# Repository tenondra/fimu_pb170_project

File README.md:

W:/pb170_project/doc/user_manual.md

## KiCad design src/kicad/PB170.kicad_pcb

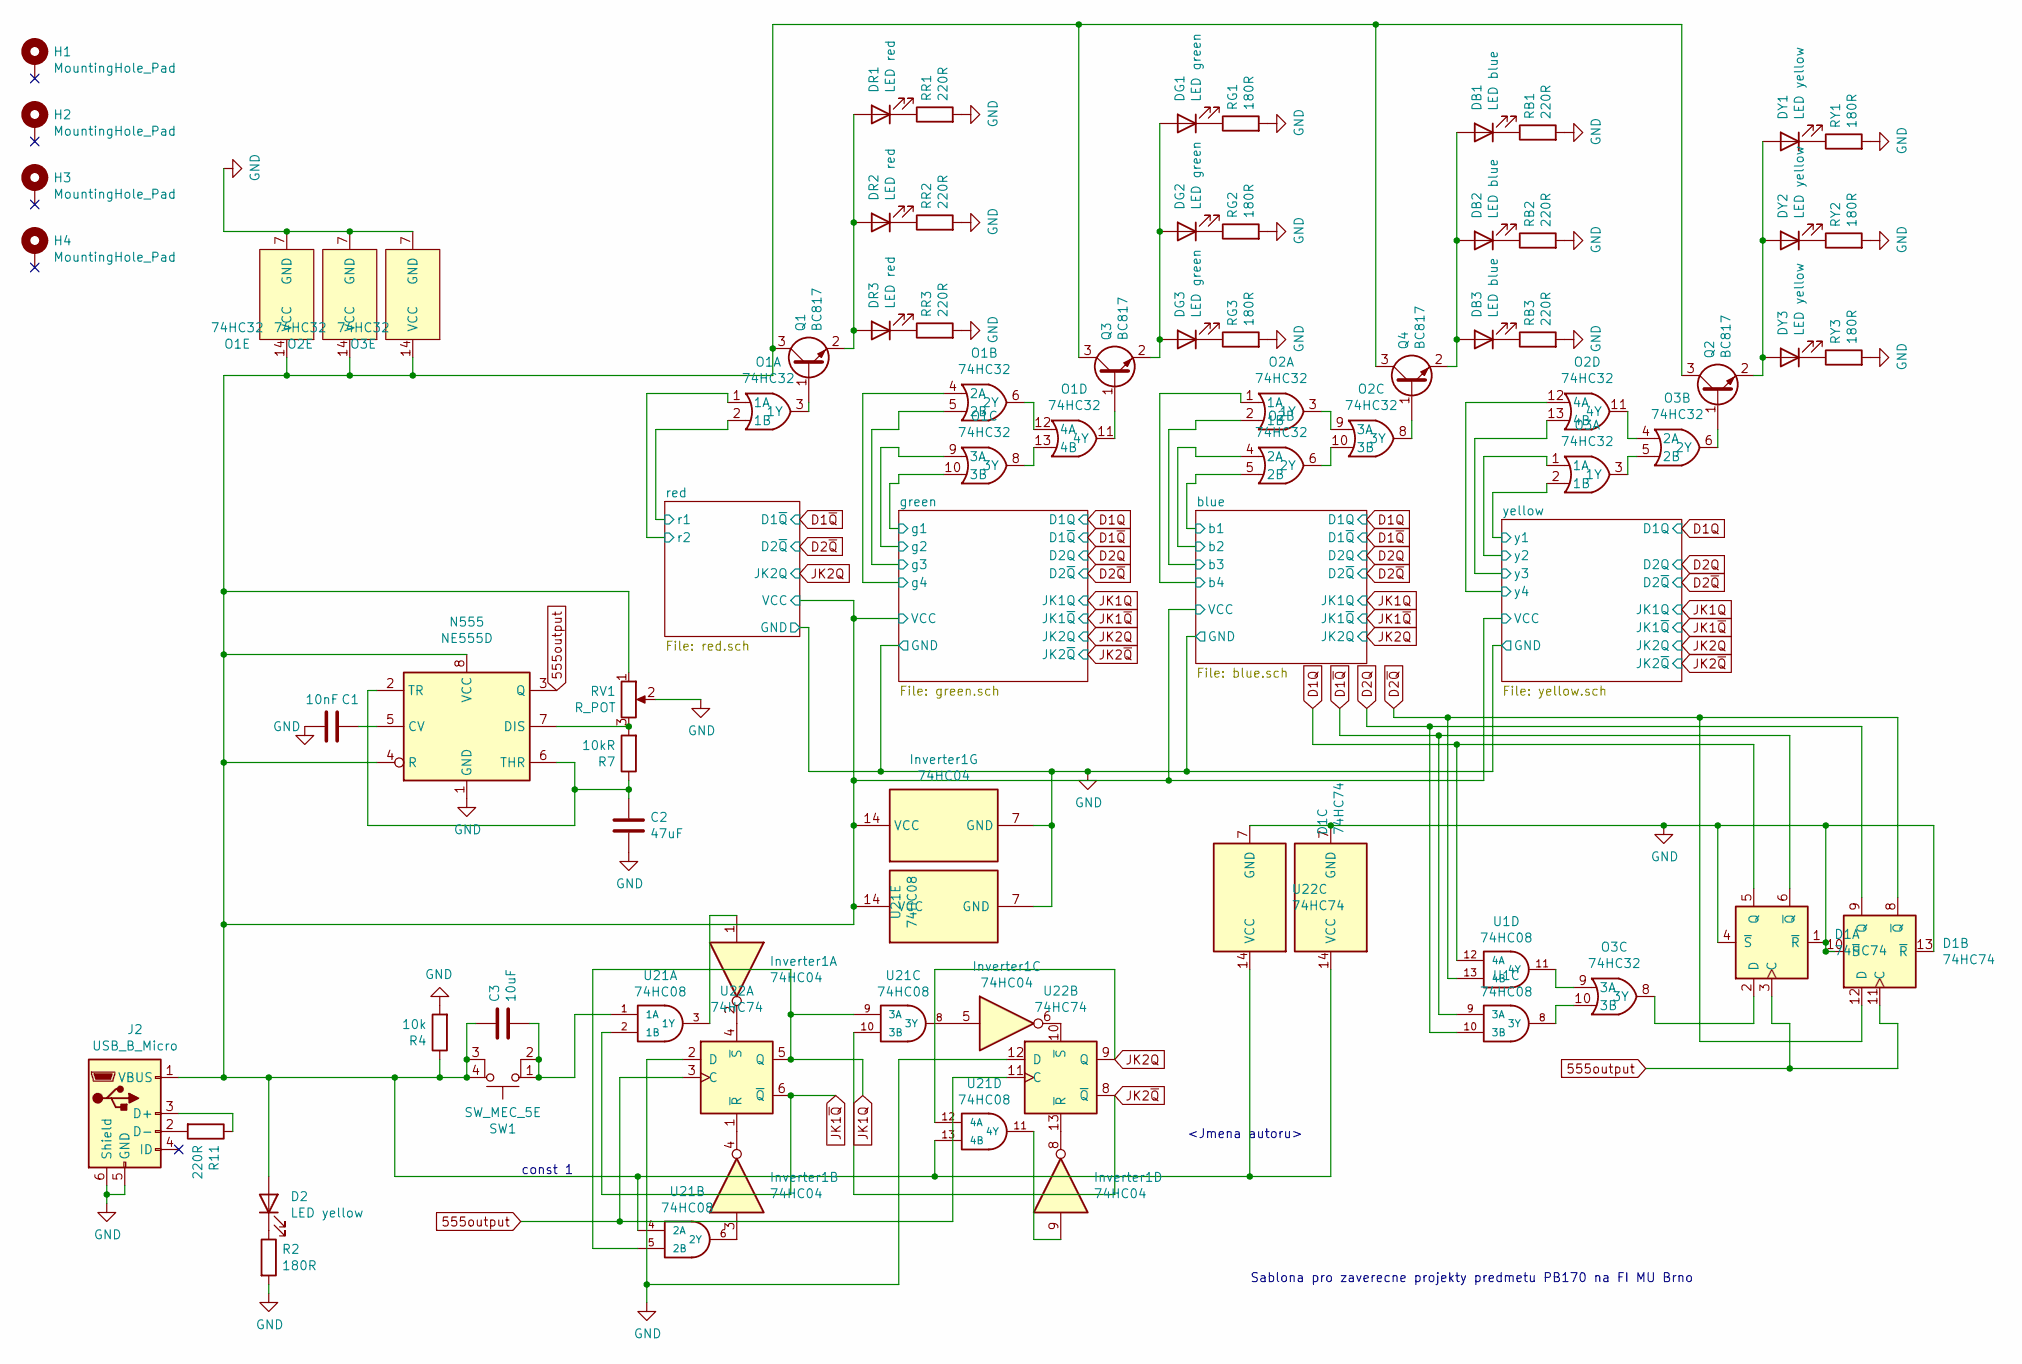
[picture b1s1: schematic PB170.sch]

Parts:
C1: 10nF; C_0805_2012Metric; LCSC C1710
C2: 47uF; C_1206_3216Metric; LCSC C96123
C3: 10uF; C_0805_2012Metric; LCSC C15850
D1: 74HC74; HTSSOP-14-1EP_4.4x5mm_P0.65mm_EP3.4x5mm_Mask3x3.1mm
D2: LED yellow; LED_0603_1608Metric; LCSC C72038
DB1, DB2, DB3: LED blue; LED_0603_1608Metric; LCSC C72041
DG1, DG2, DG3: LED green; LED_0603_1608Metric; LCSC C72043
DR1, DR2, DR3: LED red; LED_0603_1608Metric; LCSC C2286
DY1, DY2, DY3: LED yellow; LED_0603_1608Metric; LCSC C72038
H1, H2, H3, H4: MountingHole_Pad; MountingHole_3.2mm_M3_Pad
Inverter1: 74HC04; SOIC-14_3.9x8.7mm_P1.27mm
J2: USB_B_Micro; MICRO-USB-SMD_MICROXNJ; LCSC C404969
N555: NE555D; SOIC-8_3.9x4.9mm_P1.27mm; LCSC C7593
O1, O2, O3: 74HC32; SOIC-14_3.9x8.7mm_P1.27mm; LCSC C5632
Q1, Q2, Q3, Q4: BC817; SOT-23
R2: 180R; R_0603_1608Metric; LCSC C22828
R4: 10k; R_0603_1608Metric; LCSC C25804
R7: 10kR; R_0603_1608Metric; LCSC C25804
R11: 220R; R_0603_1608Metric; LCSC C22962
RB1, RB2, RB3: 220R; R_0603_1608Metric; LCSC C22962
RG1, RG2, RG3: 180R; R_0603_1608Metric; LCSC C22828
RR1, RR2, RR3: 220R; R_0603_1608Metric; LCSC C22962
RV1: R_POT; potentiometer10k; LCSC C132879
RY1, RY2, RY3: 180R; R_0603_1608Metric; LCSC C22828
SW1: SW_MEC_5E; TactileSwitch_C381064; LCSC C381064
U1, U21: 74HC08; SOIC-14_3.9x8.7mm_P1.27mm; LCSC C5593
U22: 74HC74; HTSSOP-14-1EP_4.4x5mm_P0.65mm_EP3.4x5mm_Mask3x3.1mm; LCSC C6761

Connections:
555output: D1.3 (C), D1.11 (C), N555.3 (Q), U22.3 (C), U22.11 (C)
/blue/VCC: C3.1, D1.14 (VCC), D2.2 (A), Inverter1.14 (VCC), J2.1 (VBUS), N555.4 (R), N555.8 (VCC), O1.14 (VCC), O2.14 (VCC), O3.14 (VCC), Q1.3 (C), Q2.3 (C), Q3.3 (C), Q4.3 (C), R4.1, RV1.1, SW1.3 (K), SW1.4 (A), U21.4 (2A), U21.13 (4B), U21.14 (VCC), U22.14 (VCC); also elsewhere on the board
/blue/b1: O2.5 (2B); also elsewhere on the board
/blue/b2: O2.4 (2A); also elsewhere on the board
/blue/b3: O2.2 (1B); also elsewhere on the board
/blue/b4: O2.1 (1A); also elsewhere on the board
/green/g1: O1.10 (3B); also elsewhere on the board
/green/g2: O1.9 (3A); also elsewhere on the board
/green/g3: O1.5 (2B); also elsewhere on the board
/green/g4: O1.4 (2A); also elsewhere on the board
/red/r1: O1.2 (1B); also elsewhere on the board
/red/r2: O1.1 (1A); also elsewhere on the board
/yellow/y1: O3.2 (1B); also elsewhere on the board
/yellow/y2: O3.1 (1A); also elsewhere on the board
/yellow/y3: O2.13 (4B); also elsewhere on the board
/yellow/y4: O2.12 (4A); also elsewhere on the board
D1Q: D1.5 (Q), U1.12 (4A); also elsewhere on the board
D1~Q: D1.6 (~Q), U1.9 (3A); also elsewhere on the board
D2Q: D1.9 (Q), U1.10 (3B); also elsewhere on the board
D2~Q: D1.8 (~Q), D1.12 (D), U1.13 (4B); also elsewhere on the board
GND: C1.2, C2.2, D1.1 (~R), D1.4 (~S), D1.7 (GND), D1.10 (~S), D1.13 (~R), Inverter1.7 (GND), J2.5 (GND), J2.6 (Shield), N555.1 (GND), O1.7 (GND), O2.7 (GND), O3.7 (GND), R2.2, R4.2, RB1.2, RB2.2, RB3.2, RG1.2, RG2.2, RG3.2, RR1.2, RR2.2, RR3.2, RV1.2, RY1.2, RY2.2, RY3.2, U21.7 (GND), U22.2 (D), U22.7 (GND), U22.12 (D); also elsewhere on the board
JK1Q: U21.5 (2B), U21.9 (3A), U22.5 (Q); also elsewhere on the board
JK1~Q: U21.2 (1B), U22.6 (~Q); also elsewhere on the board
JK2Q: U21.12 (4A), U22.9 (Q); also elsewhere on the board
JK2~Q: U21.10 (3B), U22.8 (~Q); also elsewhere on the board
unnamed: C1.1, N555.5 (CV)
unnamed: C2.1, N555.2 (TR), N555.6 (THR), R7.1
unnamed: C3.2, SW1.1, SW1.2, U21.1 (1A)
unnamed: D1.2 (D), O3.8 (3Y)
unnamed: D2.1 (K), R2.1
unnamed: DB1.1 (K), RB1.1
unnamed: DB1.2 (A), DB2.2 (A), DB3.2 (A), Q4.2 (E)
unnamed: DB2.1 (K), RB2.1
unnamed: DB3.1 (K), RB3.1
unnamed: DG1.1 (K), RG1.1
unnamed: DG1.2 (A), DG2.2 (A), DG3.2 (A), Q3.2 (E)
unnamed: DG2.1 (K), RG2.1
unnamed: DG3.1 (K), RG3.1
unnamed: DR1.1 (K), RR1.1
unnamed: DR1.2 (A), DR2.2 (A), DR3.2 (A), Q1.2 (E)
unnamed: DR2.1 (K), RR2.1
unnamed: DR3.1 (K), RR3.1
unnamed: DY1.1 (K), RY1.1
unnamed: DY1.2 (A), DY2.2 (A), DY3.2 (A), Q2.2 (E)
unnamed: DY2.1 (K), RY2.1
unnamed: DY3.1 (K), RY3.1
unnamed: Inverter1.1, U21.3 (1Y)
unnamed: Inverter1.2, U22.4 (~S)
unnamed: Inverter1.3, U21.6 (2Y)
unnamed: Inverter1.4, U22.1 (~R)
unnamed: Inverter1.5, U21.8 (3Y)
unnamed: Inverter1.6, U22.10 (~S)
unnamed: Inverter1.8, U22.13 (~R)
unnamed: Inverter1.9, U21.11 (4Y)
unnamed: J2.2 (D-), R11.2
unnamed: J2.3 (D+), R11.1
unnamed: N555.7 (DIS), R7.2, RV1.3
unnamed: O1.3 (1Y), Q1.1 (B)
unnamed: O1.11 (4Y), Q3.1 (B)
unnamed: O1.6 (2Y), O1.12 (4A)
unnamed: O1.8 (3Y), O1.13 (4B)
unnamed: O2.3 (1Y), O2.9 (3A)
unnamed: O2.8 (3Y), Q4.1 (B)
unnamed: O2.6 (2Y), O2.10 (3B)
unnamed: O2.11 (4Y), O3.4 (2A)
unnamed: O3.3 (1Y), O3.5 (2B)
unnamed: O3.6 (2Y), Q2.1 (B)
unnamed: O3.9 (3A), U1.11 (4Y)
unnamed: O3.10 (3B), U1.8 (3Y)

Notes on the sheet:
Sablona pro zaverecne projekty predmetu PB170 na FI MU Brno
<Jmena autoru>
const 1

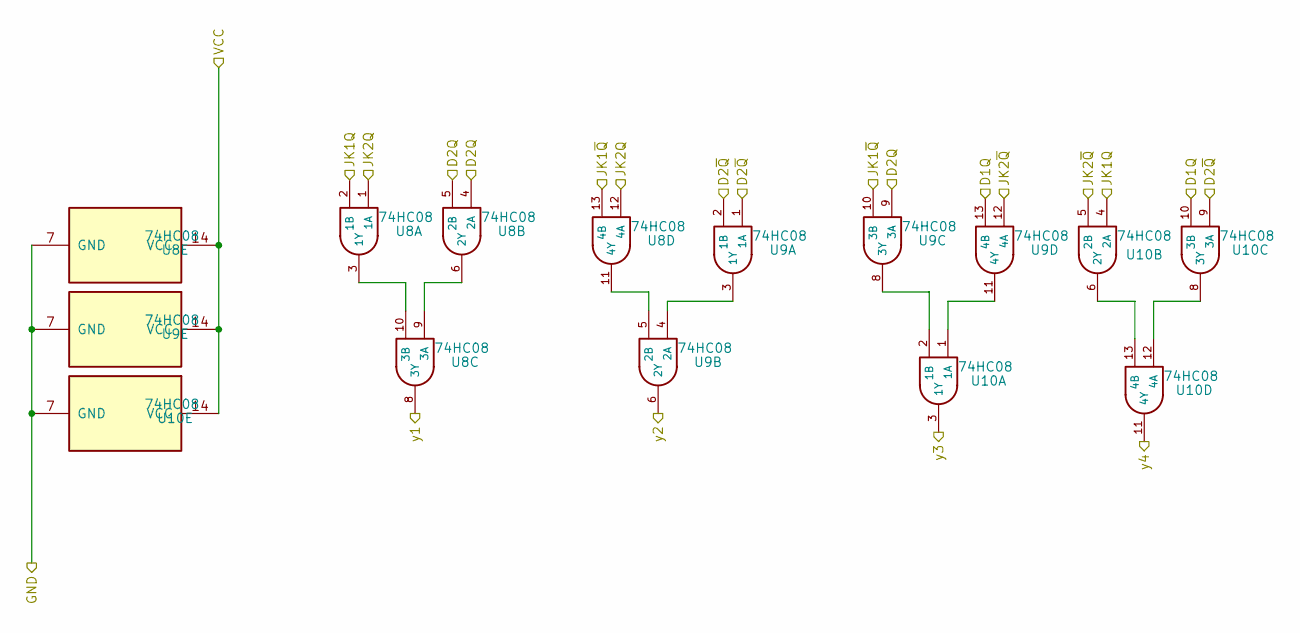
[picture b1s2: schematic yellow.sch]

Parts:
U8, U9, U10: 74HC08; SOIC-14_3.9x8.7mm_P1.27mm; LCSC C5593

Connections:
/blue/VCC: U8.14 (VCC), U9.14 (VCC), U10.14 (VCC); also elsewhere on the board
/yellow/y1: U8.8 (3Y); also elsewhere on the board
/yellow/y2: U9.6 (2Y); also elsewhere on the board
/yellow/y3: U10.3 (1Y); also elsewhere on the board
/yellow/y4: U10.11 (4Y); also elsewhere on the board
D1Q: U9.13 (4B), U10.10 (3B); also elsewhere on the board
D2Q: U8.4 (2A), U8.5 (2B), U9.9 (3A); also elsewhere on the board
D2~Q: U9.1 (1A), U9.2 (1B), U10.9 (3A); also elsewhere on the board
GND: U8.7 (GND), U9.7 (GND), U10.7 (GND); also elsewhere on the board
JK1Q: U8.2 (1B), U10.4 (2A); also elsewhere on the board
JK1~Q: U8.13 (4B), U9.10 (3B); also elsewhere on the board
JK2Q: U8.1 (1A), U8.12 (4A); also elsewhere on the board
JK2~Q: U9.12 (4A), U10.5 (2B); also elsewhere on the board
unnamed: U8.6 (2Y), U8.9 (3A)
unnamed: U8.3 (1Y), U8.10 (3B)
unnamed: U8.11 (4Y), U9.5 (2B)
unnamed: U9.3 (1Y), U9.4 (2A)
unnamed: U9.11 (4Y), U10.1 (1A)
unnamed: U9.8 (3Y), U10.2 (1B)
unnamed: U10.8 (3Y), U10.12 (4A)
unnamed: U10.6 (2Y), U10.13 (4B)

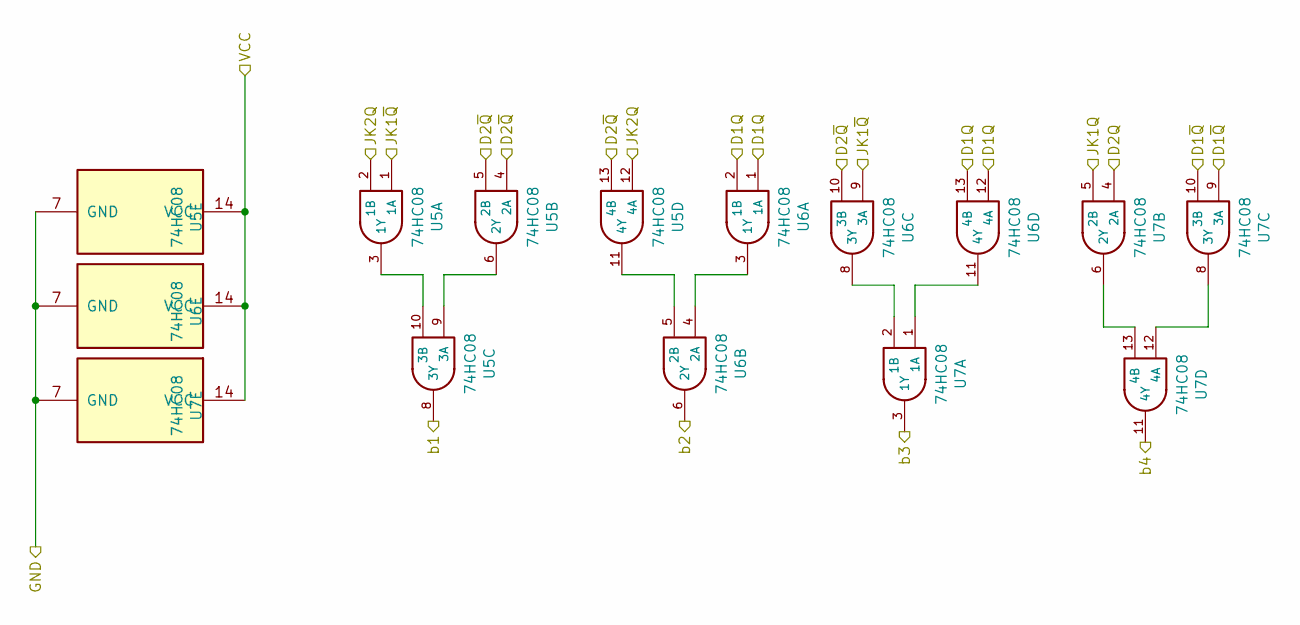
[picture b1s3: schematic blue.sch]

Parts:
U5, U6, U7: 74HC08; SOIC-14_3.9x8.7mm_P1.27mm; LCSC C5593

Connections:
/blue/VCC: U5.14 (VCC), U6.14 (VCC), U7.14 (VCC); also elsewhere on the board
/blue/b1: U5.8 (3Y); also elsewhere on the board
/blue/b2: U6.6 (2Y); also elsewhere on the board
/blue/b3: U7.3 (1Y); also elsewhere on the board
/blue/b4: U7.11 (4Y); also elsewhere on the board
D1Q: U6.1 (1A), U6.2 (1B), U6.12 (4A), U6.13 (4B); also elsewhere on the board
D1~Q: U7.9 (3A), U7.10 (3B); also elsewhere on the board
D2Q: U7.4 (2A); also elsewhere on the board
D2~Q: U5.4 (2A), U5.5 (2B), U5.13 (4B), U6.10 (3B); also elsewhere on the board
GND: U5.7 (GND), U6.7 (GND), U7.7 (GND); also elsewhere on the board
JK1Q: U7.5 (2B); also elsewhere on the board
JK1~Q: U5.1 (1A), U6.9 (3A); also elsewhere on the board
JK2Q: U5.2 (1B), U5.12 (4A); also elsewhere on the board
unnamed: U5.6 (2Y), U5.9 (3A)
unnamed: U5.3 (1Y), U5.10 (3B)
unnamed: U5.11 (4Y), U6.5 (2B)
unnamed: U6.3 (1Y), U6.4 (2A)
unnamed: U6.8 (3Y), U7.2 (1B)
unnamed: U6.11 (4Y), U7.1 (1A)
unnamed: U7.8 (3Y), U7.12 (4A)
unnamed: U7.6 (2Y), U7.13 (4B)

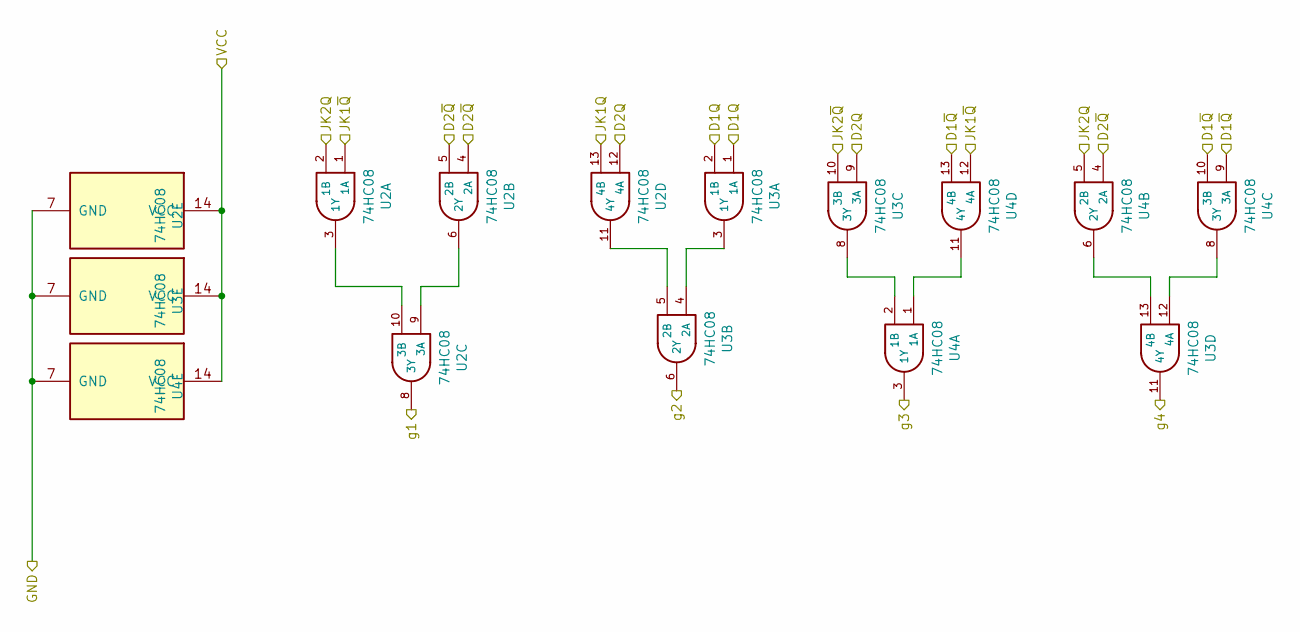
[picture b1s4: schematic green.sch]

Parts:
U2, U3, U4: 74HC08; SOIC-14_3.9x8.7mm_P1.27mm; LCSC C5593

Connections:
/blue/VCC: U2.14 (VCC), U3.14 (VCC), U4.14 (VCC); also elsewhere on the board
/green/g1: U2.8 (3Y); also elsewhere on the board
/green/g2: U3.6 (2Y); also elsewhere on the board
/green/g3: U4.3 (1Y); also elsewhere on the board
/green/g4: U3.11 (4Y); also elsewhere on the board
D1Q: U3.1 (1A), U3.2 (1B); also elsewhere on the board
D1~Q: U4.9 (3A), U4.10 (3B), U4.13 (4B); also elsewhere on the board
D2Q: U2.12 (4A), U3.9 (3A); also elsewhere on the board
D2~Q: U2.4 (2A), U2.5 (2B), U4.4 (2A); also elsewhere on the board
GND: U2.7 (GND), U3.7 (GND), U4.7 (GND); also elsewhere on the board
JK1Q: U2.13 (4B); also elsewhere on the board
JK1~Q: U2.1 (1A), U4.12 (4A); also elsewhere on the board
JK2Q: U2.2 (1B), U4.5 (2B); also elsewhere on the board
JK2~Q: U3.10 (3B); also elsewhere on the board
unnamed: U2.6 (2Y), U2.9 (3A)
unnamed: U2.3 (1Y), U2.10 (3B)
unnamed: U2.11 (4Y), U3.5 (2B)
unnamed: U3.3 (1Y), U3.4 (2A)
unnamed: U3.8 (3Y), U4.2 (1B)
unnamed: U3.12 (4A), U4.8 (3Y)
unnamed: U3.13 (4B), U4.6 (2Y)
unnamed: U4.1 (1A), U4.11 (4Y)

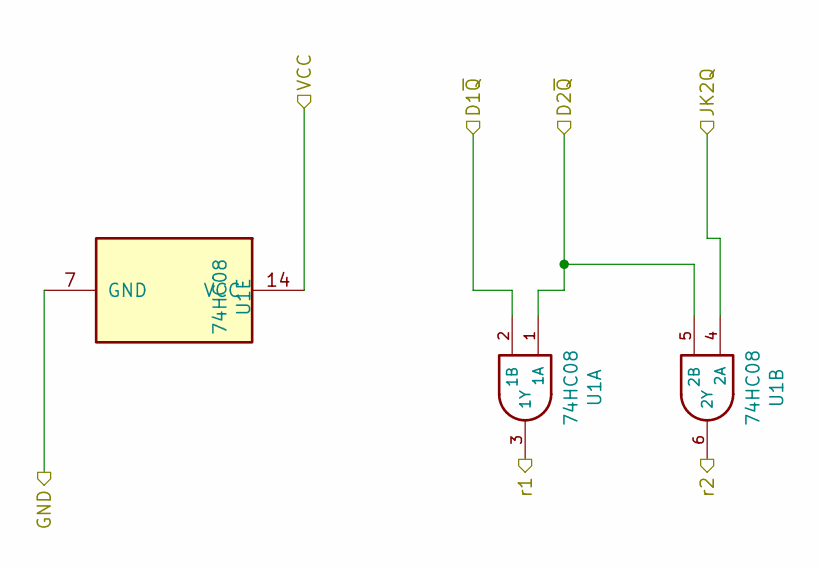
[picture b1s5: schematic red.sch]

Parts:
U1: 74HC08; SOIC-14_3.9x8.7mm_P1.27mm; LCSC C5593

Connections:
/blue/VCC: U1.14 (VCC); also elsewhere on the board
/red/r1: U1.3 (1Y); also elsewhere on the board
/red/r2: U1.6 (2Y); also elsewhere on the board
D1~Q: U1.2 (1B); also elsewhere on the board
D2~Q: U1.1 (1A), U1.5 (2B); also elsewhere on the board
GND: U1.7 (GND); also elsewhere on the board
JK2Q: U1.4 (2A); also elsewhere on the board

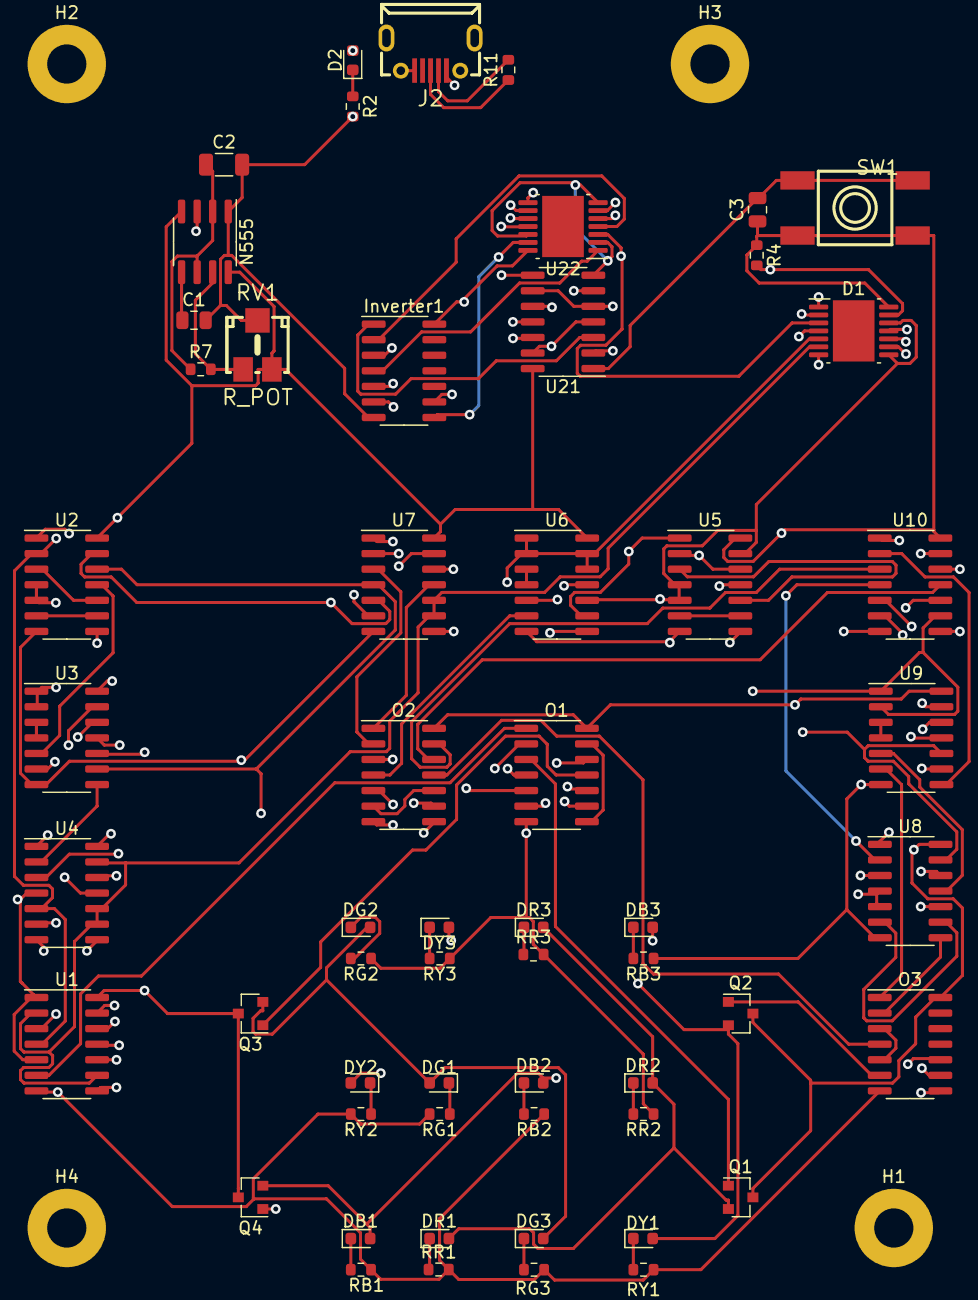
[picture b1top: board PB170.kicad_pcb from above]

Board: 4 copper layers, 61 parts (0 on the bottom side), 93 nets.

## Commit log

2020-12-10 Added initial project trials
2020-12-10 Added pb170 template, src dir for .dig files and projects
2021-01-03 Added one button switch instead two buttons
2021-01-03 Added kicad template from PB170
2021-01-03 added documentation dir
2021-01-06 First KiCad trials
2021-01-06 added basic circuit layout
2021-01-07 Corrected .digi project
2021-01-07 Changed logical OR components
2021-01-09 new OR
2021-01-10 added sub-schemes
2021-01-11 finished sub-schemes for LEDs
2021-02-04 added OR gates
2021-02-04 added D flip flops
2021-02-04 D flops edit
2021-02-07 555 clk implementation
2021-02-07 fixed annotaion
2021-02-08 Fixed wires under parts - removed
2021-02-15 Partially fixed footprint library and reassigning references
2021-02-15 added annotations, power connections to parts
2021-02-16 finished eeschema
2021-02-17 Hopefully finished eeschema, added inverters for rs flip flops
2021-02-17 removed connections from pcbnew - restarting..
2021-02-17 routing finished
2021-02-17 resolved push colisions
2021-02-19 Deleted obsolete files
2021-02-19 added docu
2021-02-19 generated proj_docu.md
2021-02-19 Added user manual and symlink for README.md
2021-02-19 Corrected negations
2021-02-26 fixed micro-usb connection, rotated the whole thing
2021-02-26 documentation edit
